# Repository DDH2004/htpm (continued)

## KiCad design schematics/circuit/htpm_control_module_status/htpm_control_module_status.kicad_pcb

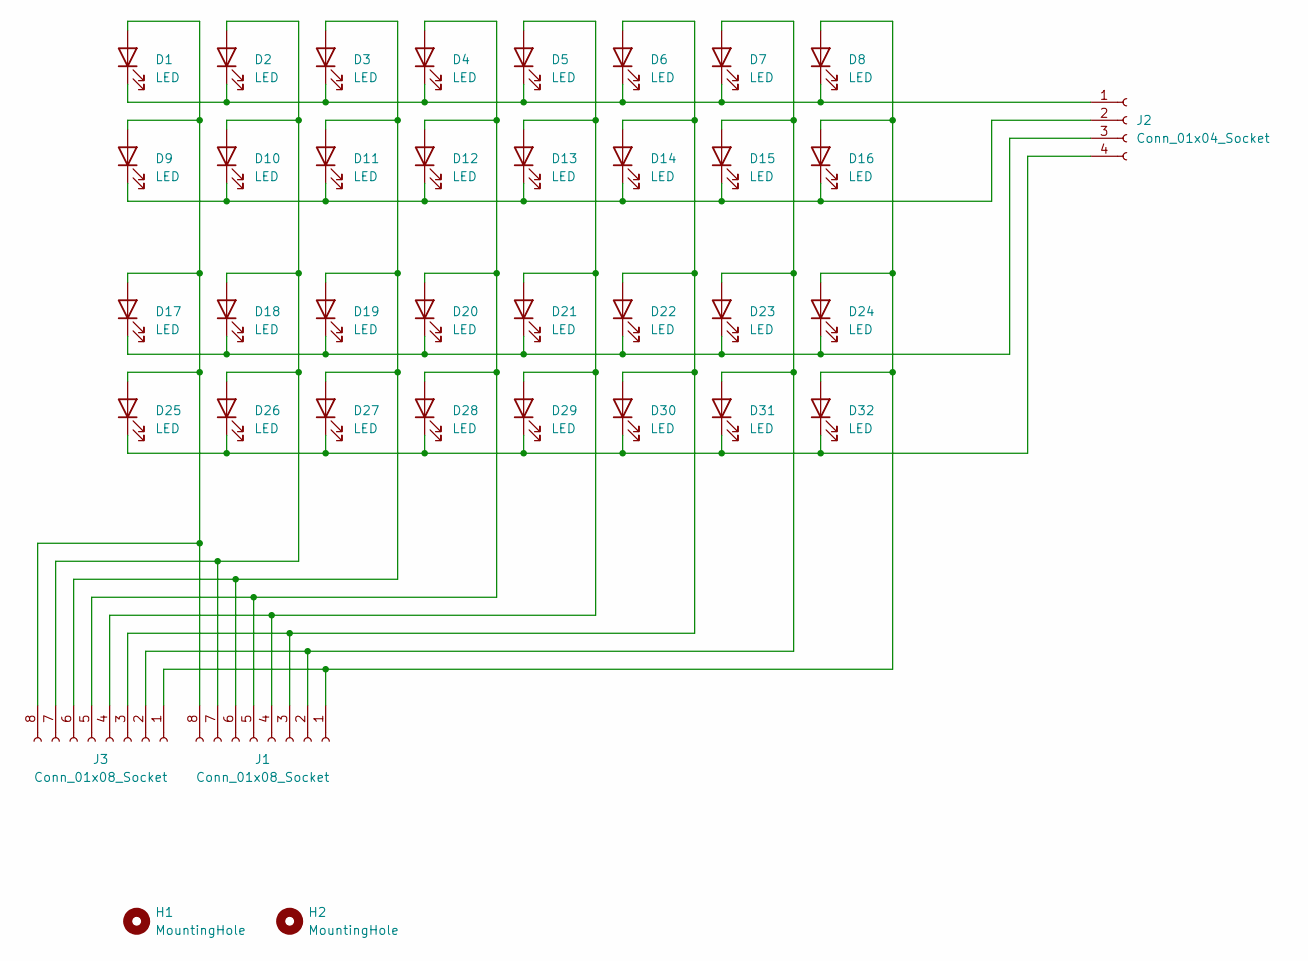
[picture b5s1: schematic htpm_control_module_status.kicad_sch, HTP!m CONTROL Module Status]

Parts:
D1, D2, D3, D4, D5, D6, D7, D8, D9, D10, D11, D12, D13, D14, D15, D16, D17, D18, D19, D20, D21, D22, D23, D24, D25, D26, D27, D28, D29, D30, D31, D32: LED; LED_D5.0mm
H1, H2: MountingHole; MountingHole_2.5mm
J1, J3: Conn_01x08_Socket; PinHeader_1x08_P2.00mm_Vertical
J2: Conn_01x04_Socket; PinHeader_1x04_P2.00mm_Vertical

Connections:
unnamed: D1.2 (A), D9.2 (A), D17.2 (A), D25.2 (A), J1.8, J3.8
unnamed: D1.1 (K), D2.1 (K), D3.1 (K), D4.1 (K), D5.1 (K), D6.1 (K), D7.1 (K), D8.1 (K), J2.1
unnamed: D2.2 (A), D10.2 (A), D18.2 (A), D26.2 (A), J1.7, J3.7
unnamed: D9.1 (K), D10.1 (K), D11.1 (K), D12.1 (K), D13.1 (K), D14.1 (K), D15.1 (K), D16.1 (K), J2.2
unnamed: D3.2 (A), D11.2 (A), D19.2 (A), D27.2 (A), J1.6, J3.6
unnamed: D4.2 (A), D12.2 (A), D20.2 (A), D28.2 (A), J1.5, J3.5
unnamed: D5.2 (A), D13.2 (A), D21.2 (A), D29.2 (A), J1.4, J3.4
unnamed: D6.2 (A), D14.2 (A), D22.2 (A), D30.2 (A), J1.3, J3.3
unnamed: D7.2 (A), D15.2 (A), D23.2 (A), D31.2 (A), J1.2, J3.2
unnamed: D8.2 (A), D16.2 (A), D24.2 (A), D32.2 (A), J1.1, J3.1
unnamed: D17.1 (K), D18.1 (K), D19.1 (K), D20.1 (K), D21.1 (K), D22.1 (K), D23.1 (K), D24.1 (K), J2.3
unnamed: D25.1 (K), D26.1 (K), D27.1 (K), D28.1 (K), D29.1 (K), D30.1 (K), D31.1 (K), D32.1 (K), J2.4

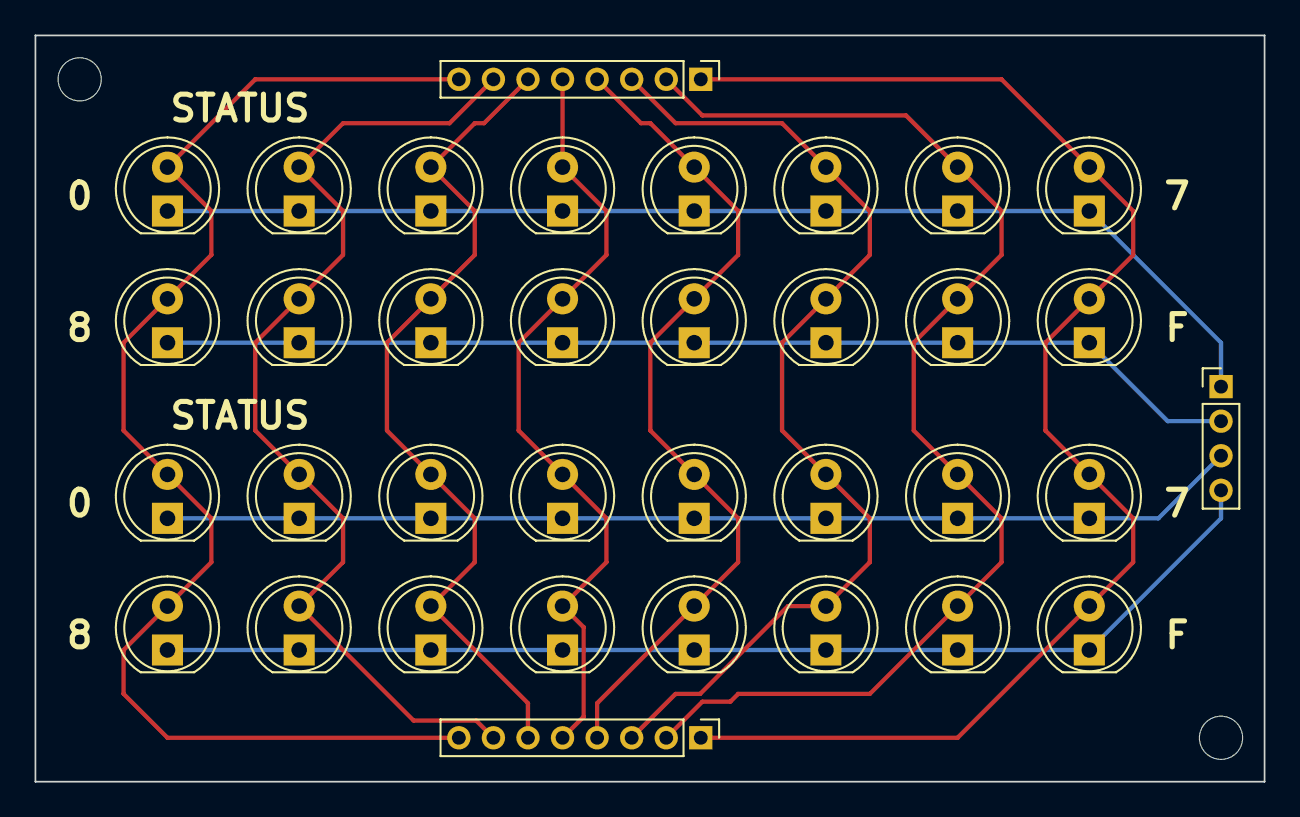
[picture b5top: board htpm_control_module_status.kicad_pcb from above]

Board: 2 copper layers, 71.1 x 43.2 mm, 37 parts (0 on the bottom side), 12 nets.

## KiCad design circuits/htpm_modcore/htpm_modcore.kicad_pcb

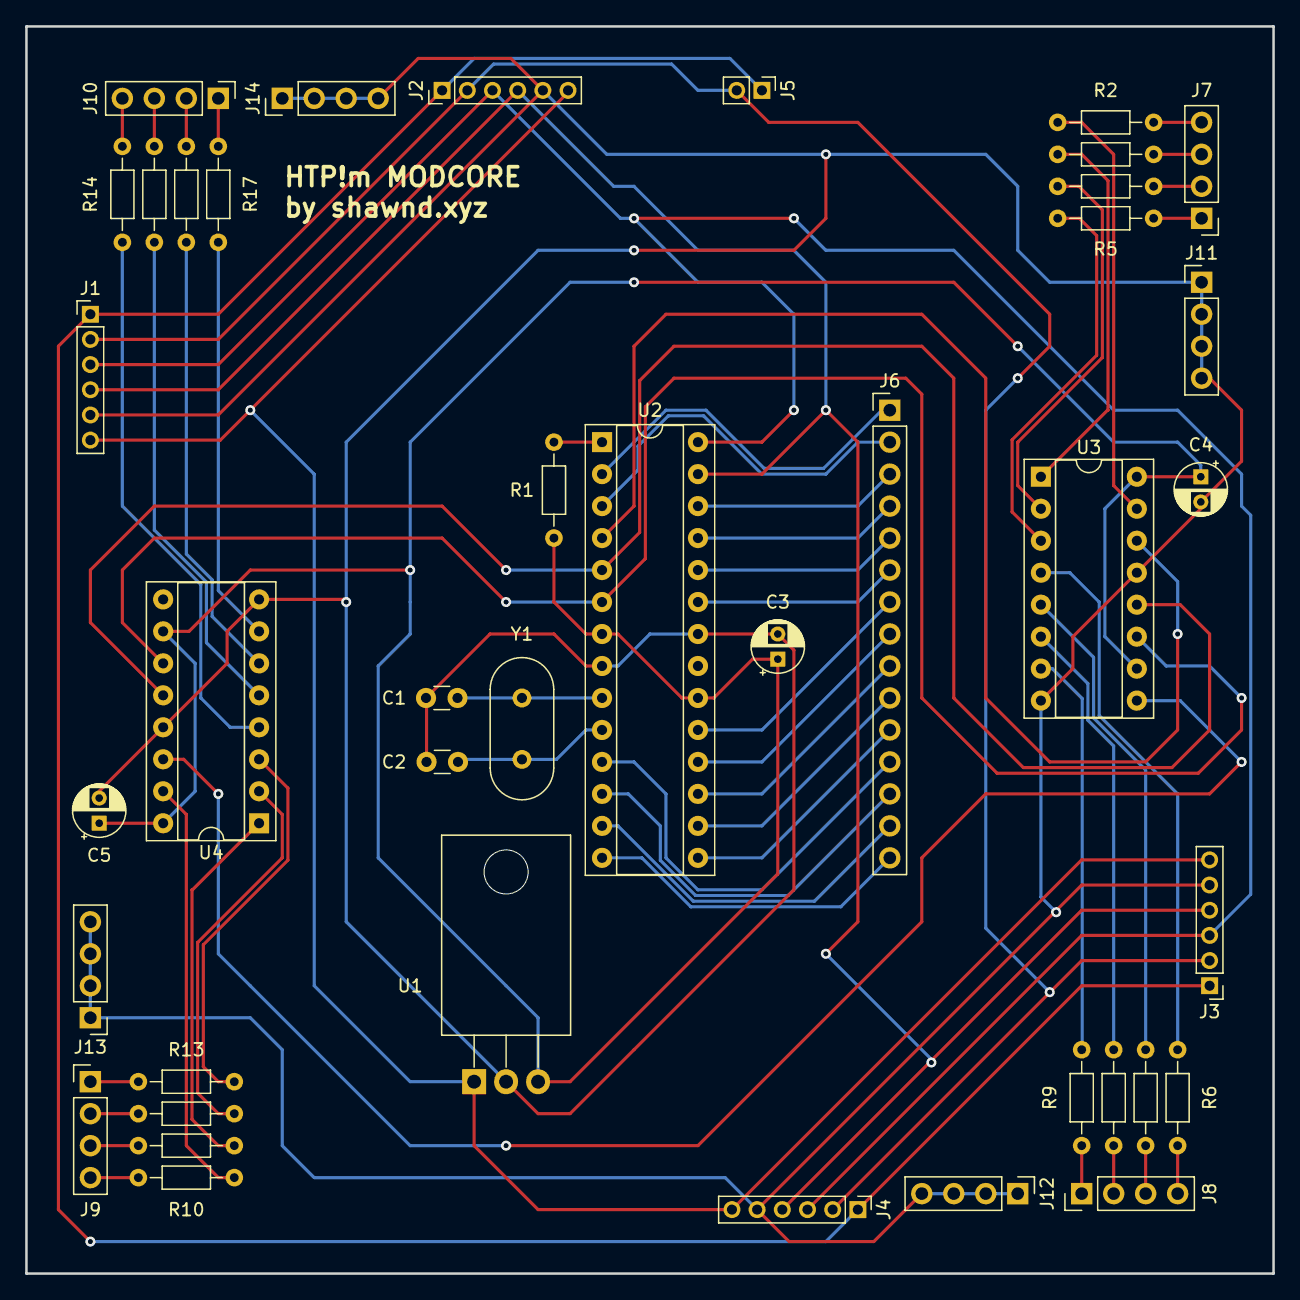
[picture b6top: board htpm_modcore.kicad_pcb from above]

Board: 2 copper layers, 99.1 x 99.1 mm, 41 parts (0 on the bottom side), 61 nets.

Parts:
C1, C2: 22pF; C_Disc_D3.0mm_W1.6mm_P2.50mm
C3: 10uF; CP_Radial_D4.0mm_P2.00mm
C4, C5: 22uF; CP_Radial_D4.0mm_P2.00mm
J1, J2, J3, J4: Conn_01x06_Pin; PinHeader_1x06_P2.00mm_Vertical
J5: Conn_01x02_Pin; PinHeader_1x02_P2.00mm_Vertical
J6: Conn_01x15_Pin; PinHeader_1x15_P2.54mm_Vertical
J7, J8, J9, J10, J11, J12, J13, J14: Conn_01x04_Pin; PinHeader_1x04_P2.54mm_Vertical
R1: 10kΩ; R_Axial_DIN0204_L3.6mm_D1.6mm_P7.62mm_Horizontal
R2, R3, R4, R5, R6, R7, R8, R9, R10, R11, R12, R13, R14, R15, R16, R17: 400Ω; R_Axial_DIN0204_L3.6mm_D1.6mm_P7.62mm_Horizontal
U1: L7805; TO-220-3_Horizontal_TabDown
U2: ATmega328-P; DIP-28_W7.62mm_Socket
U3, U4: 74HC595; DIP-16_W7.62mm_Socket
Y1: 16MHz; Crystal_HC49-U_Vertical

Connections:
GND: C1.1, C2.2, C3.2, C4.2, C5.2, J1.5, J2.5, J3.5, J4.5, J11.1, J11.2, J11.3, J11.4, J12.1, J12.2, J12.3, J12.4, J13.1, J13.2, J13.3, J13.4, J14.1, J14.2, J14.3, J14.4, U1.2 (GND), U2.8 (GND), U2.22 (GND), U3.8 (GND), U3.13 (~OE), U4.8 (GND), U4.13 (~OE)
unnamed: J1.1, J2.1, J3.1, J4.1, J5.1
unnamed: J1.2, J2.2, J3.2, J4.2, J5.2
unnamed: J1.3, J2.3, J3.3, J4.3, U2.28 (PC5)
unnamed: J1.4, J2.4, J3.4, J4.4, U2.27 (PC4)
unnamed: J1.6, J2.6, J3.6, J4.6, U1.1 (IN)
unnamed: J6.1, U2.2 (PD0)
unnamed: J6.2, U2.3 (PD1)
unnamed: J6.3, U2.26 (PC3)
unnamed: J6.4, U2.25 (PC2)
unnamed: J6.5, U2.24 (PC1)
unnamed: J6.6, U2.23 (PC0)
unnamed: J6.7, U2.19 (PB5)
unnamed: J6.8, U2.18 (PB4)
unnamed: J6.9, U2.17 (PB3)
unnamed: J6.10, U2.16 (PB2)
unnamed: J6.11, U2.15 (PB1)
unnamed: J6.12, U2.11 (PD5)
unnamed: J6.13, U2.12 (PD6)
unnamed: J6.14, U2.13 (PD7)
unnamed: J6.15, U2.14 (PB0)
unnamed: J7.1, R5.2
unnamed: J7.2, R4.2
unnamed: J7.3, R3.2
unnamed: J7.4, R2.2
unnamed: J8.1, R9.2
unnamed: J8.2, R8.2
unnamed: J8.3, R7.2
unnamed: J8.4, R6.2
unnamed: J9.1, R13.2
unnamed: J9.2, R12.2
unnamed: J9.3, R11.2
unnamed: J9.4, R10.2
unnamed: J10.1, R17.2
unnamed: J10.2, R16.2
unnamed: J10.3, R15.2
unnamed: J10.4, R14.2
unnamed: C3.1, C4.1, C5.1, R1.1, U1.3 (OUT), U2.7 (VCC), U2.20 (AVCC), U3.10 (~SRCLR), U3.16 (VCC), U4.10 (~SRCLR), U4.16 (VCC)
unnamed: U2.4 (PD2), U3.14 (SER)
unnamed: U2.5 (PD3), U3.12 (RCLK), U4.12 (RCLK)
unnamed: U2.6 (PD4), U3.11 (SRCLK), U4.11 (SRCLK)
unnamed: C1.2, U2.9 (XTAL1/PB6), Y1.2
unnamed: C2.1, U2.10 (XTAL2/PB7), Y1.1
unnamed: R1.2, U2.1 (~RESET/PC6)
unnamed: R2.1, U3.15 (QA)
unnamed: R3.1, U3.1 (QB)
unnamed: R4.1, U3.2 (QC)
unnamed: R5.1, U3.3 (QD)
unnamed: R6.1, U3.4 (QE)
unnamed: R7.1, U3.5 (QF)
unnamed: R8.1, U3.6 (QG)
unnamed: U3.9 (QH'), U4.14 (SER)
unnamed: R9.1, U3.7 (QH)
unnamed: R10.1, U4.15 (QA)
unnamed: R11.1, U4.1 (QB)
unnamed: R12.1, U4.2 (QC)
unnamed: R13.1, U4.3 (QD)
unnamed: R14.1, U4.4 (QE)
unnamed: R15.1, U4.5 (QF)
unnamed: R16.1, U4.6 (QG)
unnamed: R17.1, U4.7 (QH)

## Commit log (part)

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2023-09-23 Created HTPm MODCORE schematic and PCBs.
2023-09-24 Stopped tracking schematic backups.
2023-09-24 Created 3D CAD model of the standoff mount.
2023-09-24 Updated standoff mount CAD.
2023-09-25 Relocated gitignore.
2023-09-25 Updated HTPm MODCORE PCB.
2023-09-28 Created 3D CAD model of the module supports.
2023-09-28 Updated module support CAD.
2023-09-28 Updated mount support CAD.
2023-09-30 Organized schematics into circuit and 3D directories.
2023-09-30 Renamed module mount to module support.
2023-09-30 Created terminal support CAD.
2023-10-01 Created Pi holder CAD.
2023-10-01 Created frame CAD.
2023-10-01 Created HTPm MODCORE mount CAD.
2023-10-02 Created README.md for 3D CADs.
2023-10-02 Updated 3D CAD README.md.
2023-10-03 Created set plan CAD.
2023-10-04 Implemented I2C receive in HTPm MODCORE firmware.
2023-10-04 Formatting changes.
2023-10-04 Implemented preamble check.
2023-10-04 Implemented length and end marker validation.
2023-10-04 Implemented CRC-8 check.
2023-10-04 Fixed typo.
2023-10-04 Updated CRC-8 calculation parameters.
2023-10-05 Modified the packet encapsulation specifications.
2023-10-05 Added error check for packet MTYPE.
2023-10-05 Renamed validate_message function and implemented some debug prints.
2023-10-05 Added MTYPE-based length validation tests.
2023-10-05 Finished the rest of the debug print messages.
2023-10-06 Initial web commit.
2023-10-07 Clarified comments and changed TSET len.
2023-10-07 Created Message class.
2023-10-07 Implemented validation method.
2023-10-07 Made crc8 its own method.
2023-10-07 Created Ping class.
2023-10-07 Created Ack class.
2023-10-07 Created Actuation class.
2023-10-07 Created Tmask class.
2023-10-07 Increased TSET index to 8 bits.
2023-10-07 Created Tset class.
2023-10-07 Skipped the register byte in the firmware upon I2C receive.
2023-10-07 Created I2C class.
2023-10-07 Changed TSET length check.
2023-10-07 Fixed protocol MID and MTYPE formatting.
2023-10-07 Updated TSET debug printing format.
2023-10-07 Added HTPm CONTROL example code.
2023-10-07 Created HTPm CONTROL module display circuit.
2023-10-07 Updated info for the PCB design.
2023-10-07 Added boilerplate platform backend code.
2023-10-07 Implemented team creation.
2023-10-07 Implemented RUD methods for Team.
2023-10-07 Renamed database.
2023-10-07 Implemented CRUD for players.
2023-10-08 Created HTPm CONTROL module display PCB.
2023-10-08 Created HTPm CONTROL module display Gerbers.
2023-10-08 Renamed HTPm CONTROL Display to HTPm CONTROL Module Display.
2023-10-08 Updated comments on the HTPm CONTROL Module Display.
2023-10-08 Created HTPm CONTROL Module Status schematic.
2023-10-08 Updated text to be on silkscreen layer.
2023-10-08 Updated text location and specified product number placement.
2023-10-08 Created HTPm CONTROL Module Status PCB.
2023-10-08 Generated Gerbers.
2023-10-08 Condensed HTPm CONTROL Module Status PCB.
2023-10-08 Condensed HTPm CONTROL Module Display PCB.
2023-10-08 Repositioned HTPm CONTROL Module Display PCB.
2023-10-08 Got rid of obvious annotations.
2023-10-08 Added user-facing text to HTPm CONTROL Module Status PCB.
2023-10-08 Updated branding on the HTPm CONTROL Module Status PCB.
2023-10-08 Added user-facing text to HTPm CONTROL Module Display PCB.
2023-10-08 Updated print number formatting on HTPm CONTROL Module Status PCB.
2023-10-08 Added HTPm CONTROL Module Display and Status to masterplan.
2023-10-09 Created HTPm CONTROL Numericals schematic.
2023-10-09 Added footprints to the PCB design.
2023-10-09 Implemented CRUD for challenges - Jet
2023-10-10 Created test for POST /api/manage/teams create.
2023-10-10 Created test for GET /api/manage/teams.
2023-10-10 Updated Flask .gitignore.
2023-10-10 Removed old test script.
2023-10-10 Create test for POST /api/manage/teams update.
2023-10-10 Created HTPm CONTROL Numericals PCB.
2023-10-10 Updated silkscreen on the HTPm CONTROL Numericals PCB.
2023-10-10 Regenerated Gerbers.
2023-10-10 Added HTPm CONTROL Numericals to the masterplan.
2023-10-10 Converted spaces to tabs.
2023-10-12 Added macos files to .gitignore.
2023-10-12 Created basic website layout and simple implementation of typewriter effect.
2023-10-14 Organized 3D CADs into separate types of folders.
2023-10-14 theater cad file
2023-10-14 Updated recommended R and V values.
2023-10-14 Updated circuit annotations.
2023-10-15 Created ESP8266 logic for WAP.
2023-10-15 Updated HTPm MODCORE nominal resistance values.
2023-10-15 Updated nominal values.
2023-10-15 Updated .gitignore.
2023-10-15 Created HTPm CONTROL Additional Info schematic.
2023-10-16 Created HTPm CONTROL Additional Info PCB.
2023-10-16 Updated annotations.
2023-10-16 Created Gerbers for the HTPm CONTROL Additional Info PCB.
2023-10-16 Updated masterplan.
2023-10-16 Updated HTPm CONTROL masterplan.
2023-10-16 Restructured directories.
2023-10-16 Cleaned up models directory.
2023-10-17 hollowed out theater
    with stl and step files
2023-10-17 Parameterized the network setup.
2023-10-17 Copied WAP code for other challenges.
2023-10-18 added solves, info need help fixing issues
2023-10-18 added amtrak station
2023-10-18 hw drive in stl and step files uploaded
    also organized files to make them easier to read
2023-10-20 Added current time to login page and started basic styling.
2023-10-20 Finished login page styling.
2023-10-21 Fixed page header class.
2023-10-21 Created basic flexbox layout on home page.
2023-10-21 Fixed time display.
2023-10-21 Restructured the HTPm CONTROL schematics.
2023-10-21 Restructured the HTPm CONTROL Display schematics.
2023-10-21 reupload of stl files
2023-10-21 Moved Noor's models to the proper directory.
2023-10-21 Created a block diagram of the HTPm CONTROL.
2023-10-22 Created motherboard schematic.
2023-10-23 Created HTPm CONTROL Motherboard PCB.
2023-10-23 Changed paper size.
2023-10-23 Generated Gerbers for HTPm CONTROL Motherboard PCB.
2023-10-24 Moved the theater files to the correct directory.
2023-10-24 Moved the theater STL files to their own directory.
2023-10-24 Cleaned up STL file directory.
2023-10-24 court house stl files
2023-10-24 Updated set plan with the completed theatre footprint.
2023-10-24 Restructured set models directory.
2023-10-24 Added all components and basic styling for home page.
2023-10-25 Added min-height to page contents.
2023-10-25 Copied a theater model part to denote print readiness.
2023-10-25 Restructured Amtrak model files.
2023-10-25 court house step
2023-10-25 Updated set plan.
2023-10-25 Created splash page with typing animation.
2023-10-25 Added comments to CSS.
2023-10-25 downsized amtrak
2023-10-25 downsized hw
2023-10-26 Implemented POST in the controller.
2023-10-26 Refactored code and implemented ACKs.
2023-10-26 Merged frontend and backend.
2023-10-26 Tweaked splash page and added button link to login.
2023-10-26 Added conditional redirect for logged in users on the login page.
2023-10-26 Decreased clock update interval.
2023-10-27 Cleaned up Noor's files.
2023-10-27 added base and body hw stl files
2023-10-27 Cleaned up Amtrak files.
2023-10-27 Cleaned up HW files.
2023-10-27 Removed bad sets.
2023-10-27 Updated set model list.
2023-10-27 Restructured challenges directory structure.
2023-10-27 made amtrak bady walls thicker
2023-10-28 Restructured Noor's files.
2023-10-28 Implemented no account button.
2023-10-28 Froze dependencies.
2023-10-28 Implemented login.
2023-10-28 Implemented admin interface.
2023-10-28 Added team name rendering to frontend.
2023-10-28 Restructured default admin account make code.
2023-10-28 Implemented admin index page.
2023-10-28 Removed unused page.
2023-10-28 Changed insufficient permissions text.
2023-10-28 Added logout button to home page.
2023-10-28 Made two pages: login and automation page
2023-10-28 Added Flask boilerplate for challenge 0.
2023-10-28 Updated the set plan.
2023-10-28 Added abilitiy for logon page to take user to app.
2023-10-28 Fixed a typo.
2023-10-30 Implemented disable lights in smart home target.
2023-10-30 Implemented notes section of vulnerable app.
2023-10-31 Created Dockerfile for Challenge 0
2023-10-31 Added logout for admin.
2023-10-31 Added views for all table types.
2023-10-31 Updated models.
2023-10-31 Removed unused parameter.
2023-10-31 Added requests to requirements.
2023-10-31 First round of smoothing for the API.
2023-10-31 Added termcolor to requirements.
2023-10-31 Added test script base code and modified API.
2023-10-31 Implemented tests for the API.
2023-10-31 Removed unused dependencies.
2023-10-31 Created a CRUD script for the platform.
2023-10-31 Implemented app page player listing.
2023-10-31 Implemented log updating.
2023-10-31 Changed log ordering.
2023-10-31 Handled keyboard interrupts in the CRUD script.
2023-10-31 Added styling for logs section.
2023-11-01 Fixed overflow in logs bug.
2023-11-01 Fixed endpoints for update/delete solves in CRUD script.
2023-11-01 Implemented completion button highlight update.
2023-11-02 Added dummy yaml files (WIP)
2023-11-02 Initial implementation of vulnerable power grid target.
2023-11-02 Implemented status command in vulnerable power grid target.
2023-11-02 Simplified Makefile.
2023-11-02 Finished ScadaOS target.
2023-11-02 Updated secret location.
2023-11-02 Created Dockerfile and serve script for power grid target.
2023-11-02 Added scripts to skip and unskip secrets worktree.
2023-11-02 Created a bunch of dummy ovpns.
2023-11-02 Restructured secrets directory.
2023-11-02 Updated dummy file naming.
2023-11-02 Renamed target directory.
2023-11-02 Updated worktree skipping scripts.
2023-11-02 Restructured smart home target.
2023-11-02 Started work on a secret moving script.
2023-11-02 Renamed move script to copy script.
2023-11-02 Updated smart home target bootstrapping process.
2023-11-02 Added compose for smart home target.
2023-11-02 Updated image location in compose.
2023-11-02 Fixed pull error for private registry.
2023-11-02 Renamed firmware directory.
2023-11-02 Created dummies for smart home target.
2023-11-02 Created dummy for railroad target.
2023-11-03 Created dummies for power grid target.
2023-11-03 Added ESP8266 wap code for power grid target.
2023-11-03 Made power grid challenge deployable.
2023-11-03 Added secret templates for WAP secrets.
2023-11-03 Created template for scorebot secrets.
2023-11-03 Updated template for scorebot secrets.
2023-11-03 Implemented scorebot.
2023-11-03 Fixed wrong extensions on skip worktree scripts.
2023-11-03 Adjusted scorebot output formatting.
2023-11-03 Updated worktree skip scripts with scorebot secret location.
2023-11-03 Added t0 scorebot secret template.
2023-11-03 Created scorebot for t0.
2023-11-03 Fixed a typo in a template.
2023-11-03 Updated secret copy script.
2023-11-03 Fixed bad extension in secret copy script.
2023-11-03 Updated scorebot output formatting.
2023-11-03 Implemented scorebot for t0-htpm-t0.
2023-11-03 Added more spacing to scorebot script.
2023-11-03 Updated formatting of API outputs in t0-htpm-t0.
2023-11-03 Set up secret templates for t2-htpm-t0.
2023-11-03 Updated crud to point to live site.
2023-11-03 Added a favicon.
2023-11-03 Fixed favicon link.
2023-11-03 Updated t2 login secret.
2023-11-03 Added timestamp to scorebot.
2023-11-03 Created scorebot for t2.
2023-11-03 Increased scorebot receive amount.
2023-11-03 Added VPN move for t1-htpm-t0.
2023-11-03 Added base files for t1-htpm-t0.
2023-11-03 Added template for public SSH key secret.
2023-11-03 Added sample pubkey.
2023-11-03 Modified secret copy script to copy public SSH key.
2023-11-03 Renamed authorized_hosts to authorized_keys.
2023-11-03 Implemented scorebot for railroad target.
2023-11-03 Added scorebot to railroad target.
2023-11-03 Updated railroad scorebot to detect notes.
2023-11-03 Added an initial state.
2023-11-03 Created a velocity control app.
2023-11-03 Updated railroad management script.
2023-11-03 Updated splash page link.
2023-11-03 Updated logout color.
2023-11-03 Added instructions.
2023-11-03 Prevented page oversize.
2023-11-04 Implemented player reward for solves.
2023-11-04 Fixed a syntax error.
2023-11-04 Fixed missing dependency.
2023-11-04 Fixed incorrect method for auth.
2023-11-04 Updated challenge names in scorebot script.
